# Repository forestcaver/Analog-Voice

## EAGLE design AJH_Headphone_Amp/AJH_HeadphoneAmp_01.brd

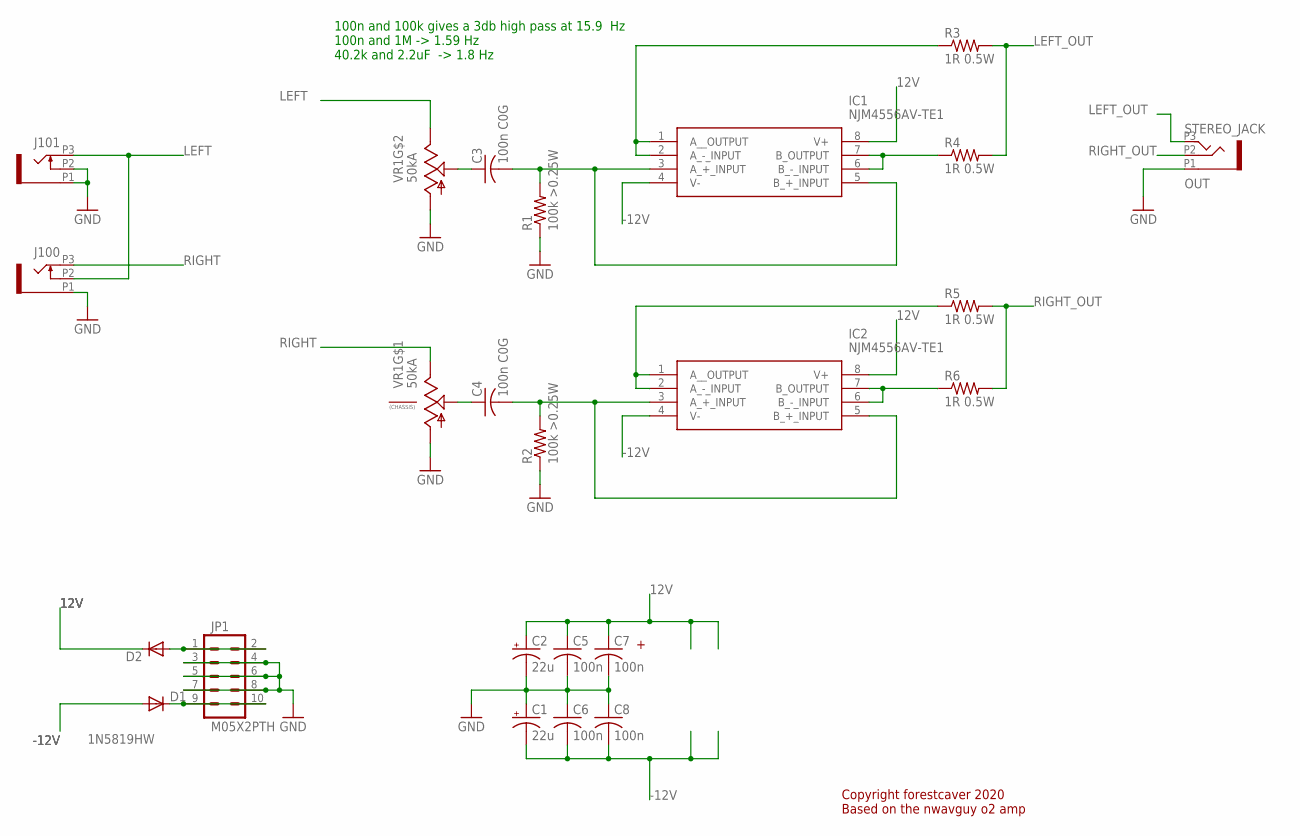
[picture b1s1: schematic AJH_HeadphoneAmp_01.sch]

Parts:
C1, C2: 22u; PANASONIC_B
C3, C4: 100n C0G; C1206
C5, C6, C7, C8: 100n; C0603
D1, D2: 1N5819HW; SOD123
IC1, IC2: NJM4556AV-TE1; SOP65P640X145-8N
J100, J101: PJ301_THONKICONN6; WQP_PJ_301M6
JP1: M05X2PTH; AVR_ICSP
OUT: STEREO_JACK; WQP_PJ_301M8
R1, R2: 100k >0.25W; R1206
R3, R4, R5, R6: 1R 0.5W; R1206
VR1: 50kA; DUAL_9MM_SNAP-IN_POT

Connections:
12V: C2.+, C5.1, C7.1, D2.C, IC1.8 (V+), IC2.8 (V+)
-12V: C1.-, C6.2, C8.2, D1.A, IC1.4 (V-), IC2.4 (V-)
GND: C1.+, C2.-, C5.2, C6.1, C7.2, C8.1, J100.P1 (1), J101.P1 (1), J101.P2 (2), JP1.3, JP1.4, JP1.5, JP1.6, JP1.7, JP1.8, OUT.P1 (1), R1.1, R2.1, VR1.1 (A), VR1.1B (A)
LEFT: J100.P2 (2), J101.P3 (3), VR1.3B (E)
LEFT_OUT: OUT.P3 (3), R3.2, R4.2
unnamed: C4.1, VR1.2 (S)
unnamed: C3.1, VR1.2B (S)
unnamed: C4.2, IC2.3 (A_+_INPUT), IC2.5 (B_+_INPUT), R2.2
unnamed: C3.2, IC1.3 (A_+_INPUT), IC1.5 (B_+_INPUT), R1.2
unnamed: IC1.6 (B_-_INPUT), IC1.7 (B_OUTPUT), R4.1
unnamed: D2.A, JP1.1, JP1.2
unnamed: IC2.1 (A__OUTPUT), IC2.2 (A_-_INPUT), R5.1
unnamed: IC2.6 (B_-_INPUT), IC2.7 (B_OUTPUT), R6.1
unnamed: IC1.1 (A__OUTPUT), IC1.2 (A_-_INPUT), R3.1
unnamed: D1.C, JP1.9, JP1.10
RIGHT: J100.P3 (3), VR1.3 (E)
RIGHT_OUT: OUT.P2 (2), R5.2, R6.2

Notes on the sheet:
100n and 100k gives a 3db high pass at 15.9 Hz 100n and 1M -> 1.59 Hz 40.2k and 2.2uF -> 1.8 Hz
Copyright forestcaver 2020 Based on the nwavguy o2 amp

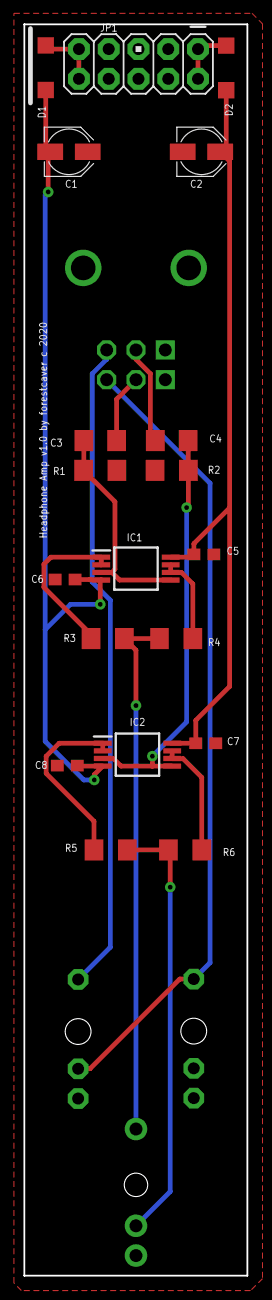
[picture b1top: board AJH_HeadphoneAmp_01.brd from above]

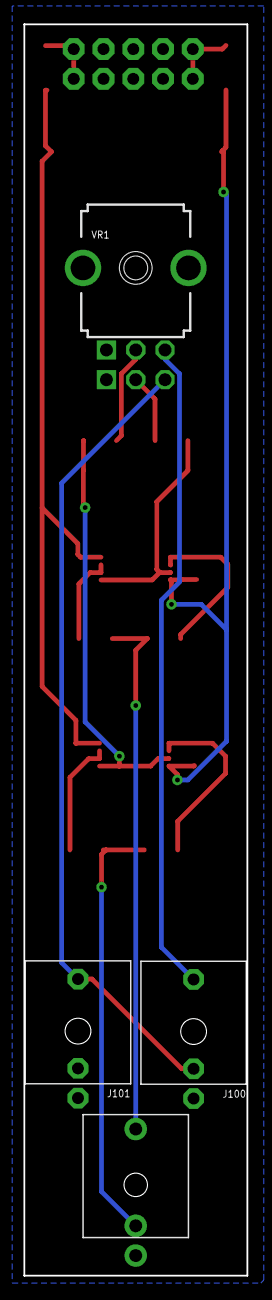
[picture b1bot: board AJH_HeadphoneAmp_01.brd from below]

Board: 2 copper layers, 19.0 x 106.8 mm, 23 parts (4 on the bottom side), 17 nets.

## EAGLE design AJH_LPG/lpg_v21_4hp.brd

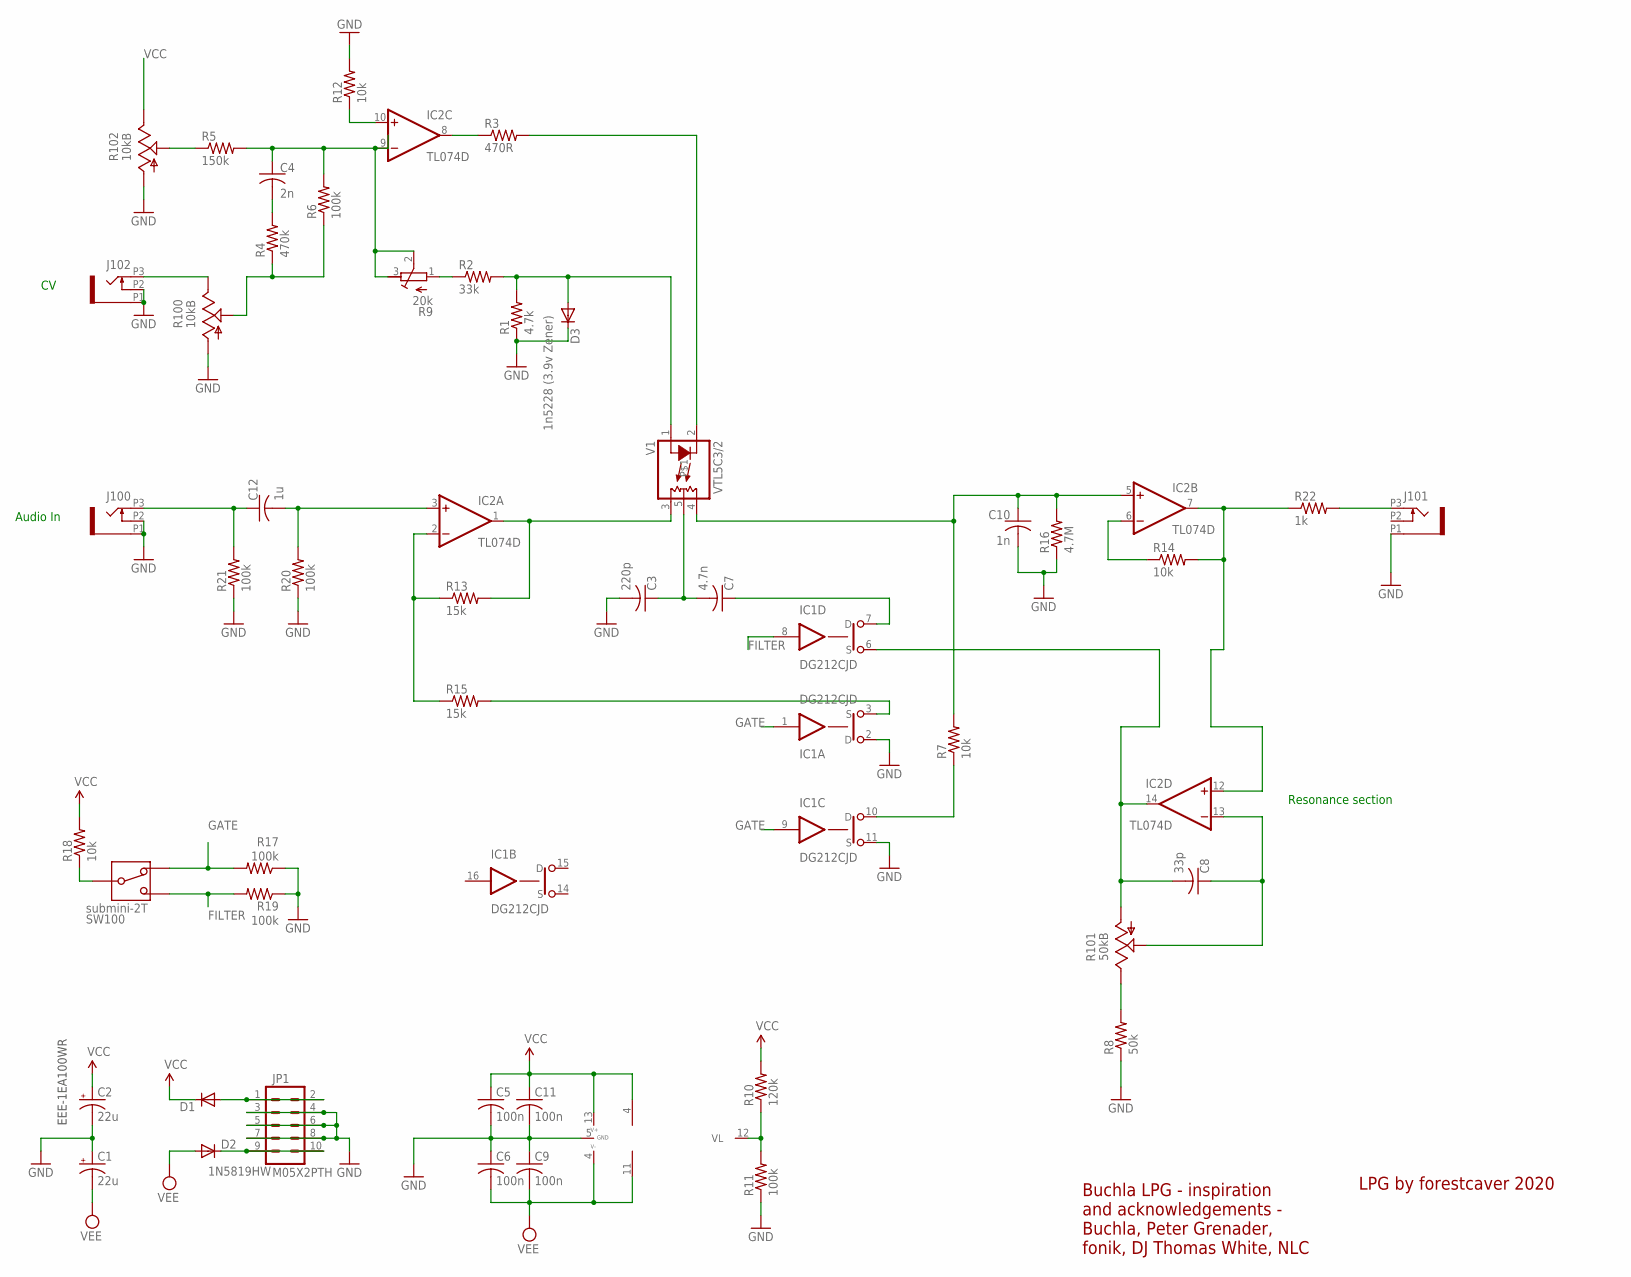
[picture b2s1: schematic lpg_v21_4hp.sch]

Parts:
C1, C2: 22u; PANASONIC_B; MPN EEE-FT1V220AR; MOUSER 667-EEE-FT1V220AR
C3: 220p; C0603
C4: 2n; C0603
C5, C6, C9, C11: 100n; C0603
C7: 4.7n; C0603
C8: 33p; C0603
C10: 1n; C0603
C12: 1u; C0603
D1, D2: 1N5819HW; SOD123
D3: 1n5228 (3.9v Zener); SOD123; MPN MMSZ5228BT1G; MOUSER 863-MMSZ5228BT1G
IC1: DG212CJD; SO16; MPN ADG212AKRZ-REEL; MOUSER 584-ADG212AKRZ-R
IC2: TL074D; SO14; MPN TL074CDR; MOUSER 595-TL074CDR
J100, J101, J102: PJ301_THONKICONN6; WQP_PJ_301M6
JP1: M05X2PTH; AVR_ICSP
R1: 4.7k; R0603
R2: 33k; R0603
R3: 470R; R0603
R4: 470k; R0603
R5: 150k; R0603
R6, R11, R17, R19, R20, R21: 100k; R0603
R7, R12, R14, R18: 10k; R0603
R8: 50k; R0603
R9: 20k; RTRIM3296X
R10: 120k; R0603
R13, R15: 15k; R0603
R16: 4.7M; R0603
R22: 1k; R0603
R100, R102: 10kB; ALPS_POT_VERTICAL_PS
R101: 50kB; ALPS_POT_VERTICAL_PS
SW100: submini-2T; SPDT-SUB
V1: VTL5C3/2; VACTROL_5PIN_VTL5C-2

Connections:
FILTER: IC1.8 (IN), R19.2, SW100.P$1
GATE: IC1.1 (IN), IC1.9 (IN), R17.2, SW100.P$3
GND: C1.+, C2.-, C3.2, C5.2, C6.1, C9.1, C10.2, C11.2, D3.C, IC1.2 (D), IC1.5 (GND), IC1.11 (S), J100.P1 (1), J100.P2 (2), J101.P1 (1), J102.P1 (1), J102.P2 (2), JP1.3, JP1.4, JP1.5, JP1.6, JP1.7, JP1.8, R1.1, R8.1, R11.1, R12.2, R16.1, R17.1, R19.1, R20.1, R21.1, R100.P$3 (A), R102.P$3 (A)
unnamed: IC1.3 (S), R15.2
unnamed: C8.2, IC1.6 (S), IC2.14 (OUT), R101.P$3 (A)
unnamed: IC1.10 (D), R7.1
unnamed: IC1.12 (VL), R10.1, R11.2
unnamed: J102.P3 (3), R100.P$1 (E)
unnamed: D1.A, JP1.1, JP1.2
unnamed: R18.1, SW100.P$2
unnamed: R5.1, R102.P$2 (S)
unnamed: C7.1, IC1.7 (D)
unnamed: C12.2, IC2.3 (+IN), R20.2
unnamed: R8.2, R101.P$1 (E)
unnamed: D2.C, JP1.9, JP1.10
unnamed: C4.2, R4.2
unnamed: R2.1, R9.1 (E)
unnamed: R4.1, R6.1, R100.P$2 (S)
unnamed: IC2.8 (OUT), R3.1
unnamed: IC2.10 (+IN), R12.1
unnamed: C4.1, IC2.9 (-IN), R5.2, R6.2, R9.2 (S), R9.3 (A)
unnamed: D3.A, R1.2, R2.2, V1.1 (A)
unnamed: R3.2, V1.2 (C)
unnamed: C12.1, J100.P3 (3), R21.2
unnamed: IC2.2 (-IN), R13.1, R15.1
unnamed: IC2.1 (OUT), R13.2, V1.3 (L1)
unnamed: C3.1, C7.2, V1.5
unnamed: J101.P3 (3), R22.2
unnamed: IC2.6 (-IN), R14.1
unnamed: IC2.7 (OUT), IC2.12 (+IN), R14.2, R22.1
unnamed: C10.1, IC2.5 (+IN), R7.2, R16.2, V1.4 (L2)
unnamed: C8.1, IC2.13 (-IN), R101.P$2 (S)
VCC: C2.+, C5.1, C11.1, D1.C, IC1.13 (V+), IC2.4 (V+), R10.2, R18.2, R102.P$1 (E)
VEE: C1.-, C6.2, C9.2, D2.A, IC1.4 (V-), IC2.11 (V-)

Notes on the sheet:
EEE-1EA100WR
Audio In
Resonance section
LPG by forestcaver 2020
Buchla LPG - inspiration and acknowledgements - Buchla, Peter Grenader, fonik, DJ Thomas White, NLC

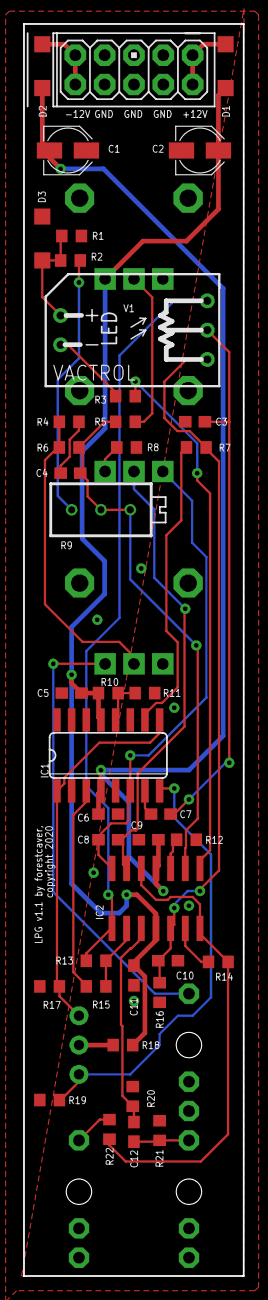
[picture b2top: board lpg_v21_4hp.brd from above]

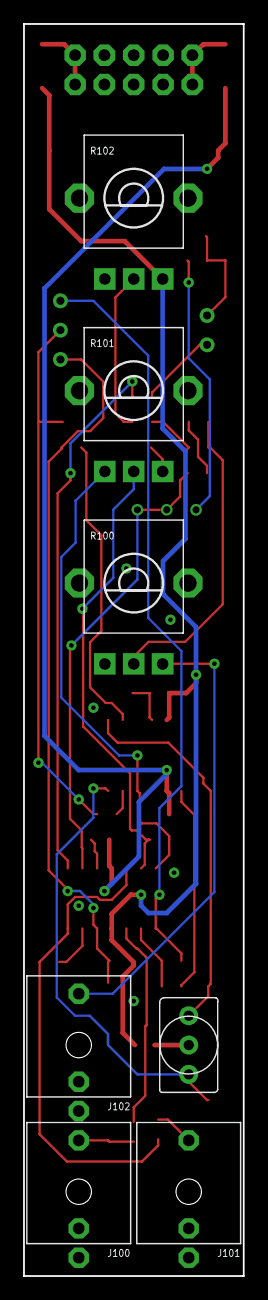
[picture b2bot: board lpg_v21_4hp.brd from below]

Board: 2 copper layers, 19.0 x 108.4 mm, 48 parts (7 on the bottom side), 34 nets.

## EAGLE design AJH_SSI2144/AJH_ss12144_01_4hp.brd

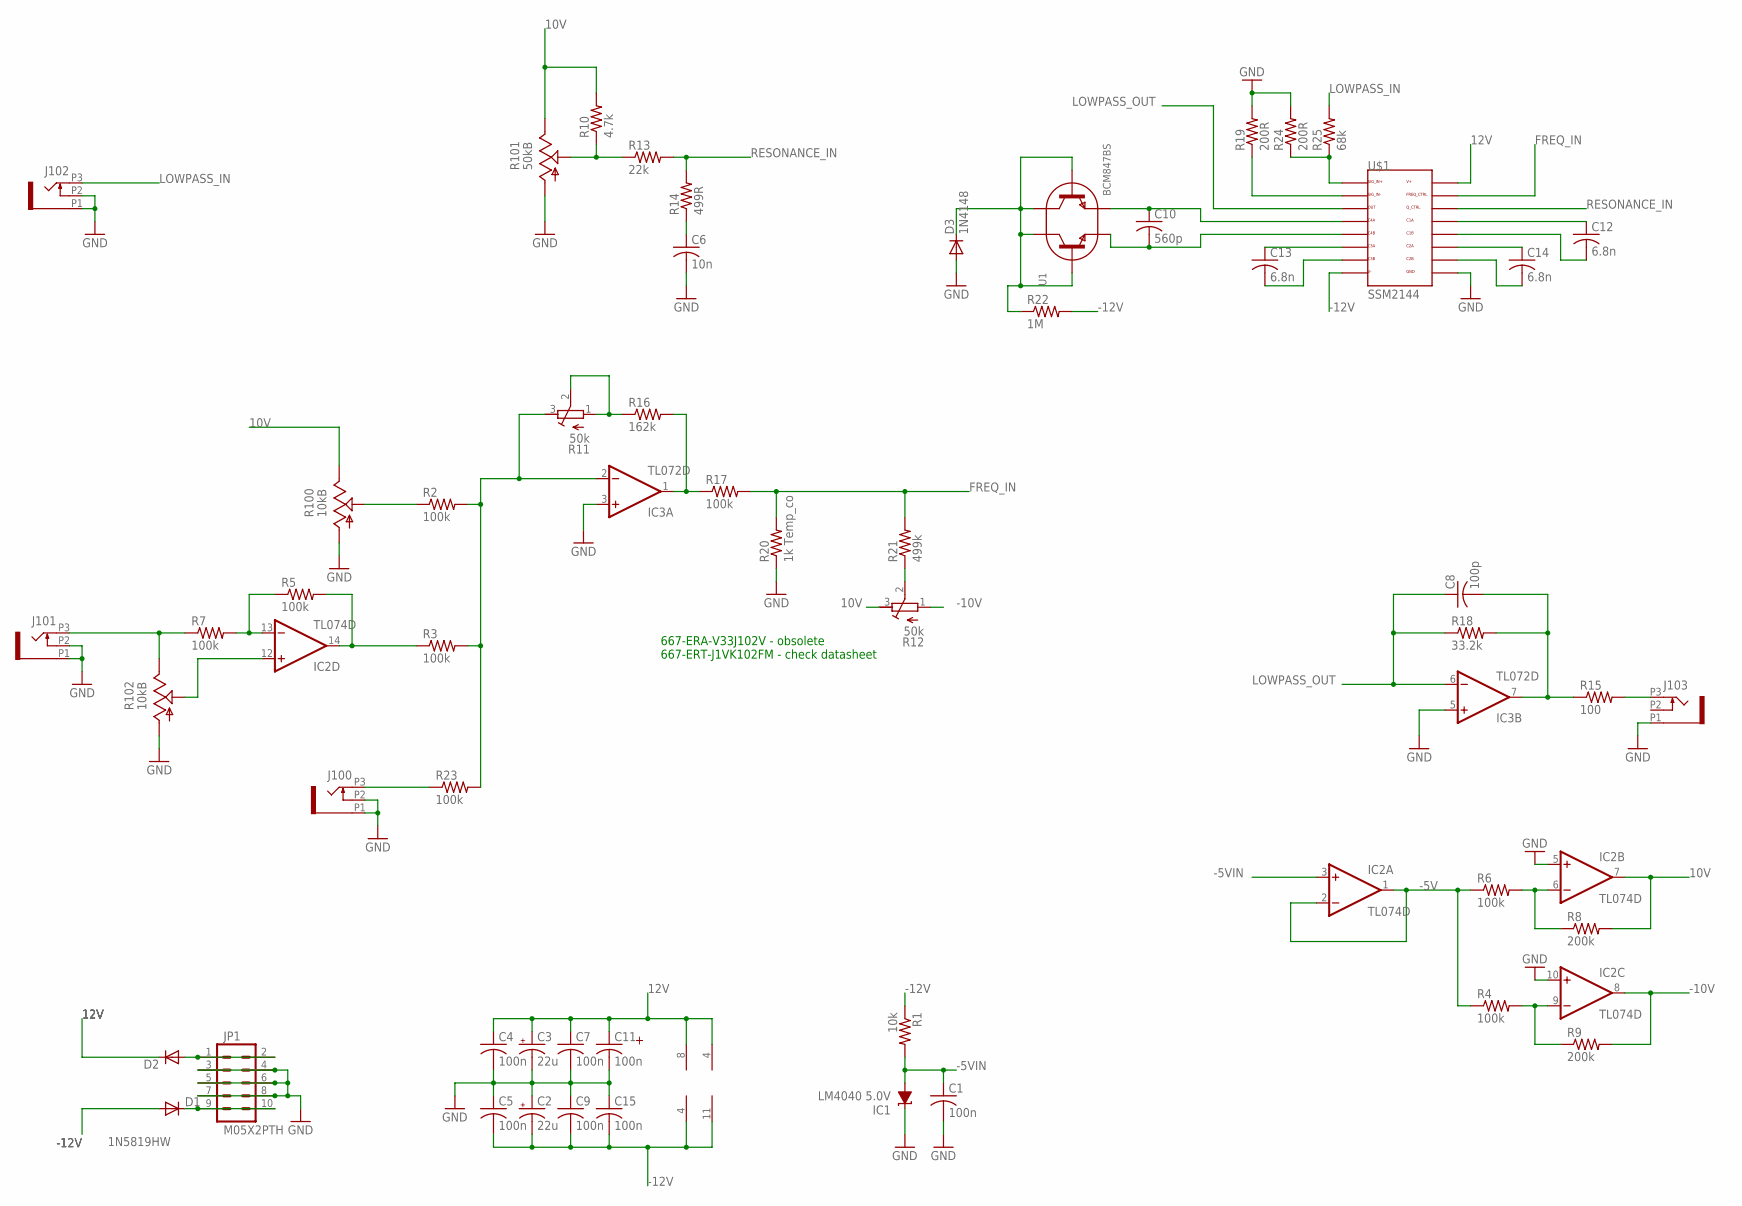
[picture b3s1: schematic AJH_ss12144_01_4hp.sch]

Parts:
C1, C4, C5, C7, C9, C11, C15: 100n; C0603
C2, C3: 22u; PANASONIC_B
C6: 10n; C0603
C8: 100p; C0603
C10: 560p; C0603
C12, C13, C14: 6.8n; C0603
D1, D2: 1N5819HW; SOD123
D3: 1N4148; SOD523
IC1: LM4040 5.0V; DBZ_R-PDSO-G3
IC2: TL074D; SO14
IC3: TL072D; SO08
J100, J101, J102, J103: PJ301_THONKICONN6; WQP_PJ_301M6
JP1: M05X2PTH; AVR_ICSP
R1: 10k; R0603
R2, R3, R4, R5, R6, R7, R17, R23: 100k; R0603
R8, R9: 200k; R0603
R10: 4.7k; R0603
R11, R12: 50k; RTRIM3296X
R13: 22k; R0603
R14: 499R; R0603
R15: 100; R0603
R16: 162k; R0603
R18: 33.2k; R0603
R19, R24: 200R; R0603
R20: 1k Temp_co; R0603
R21: 499k; R0603
R22: 1M; R0603
R25: 68k; R0603
R100, R102: 10kB; ALPS_POT_VERTICAL
R101: 50kB; ALPS_POT_VERTICAL
U1: BCM847BS; SOT363
U$1: SSM2144; SSOP16

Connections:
10V: IC2.7 (OUT), R8.2, R10.2, R12.3 (A), R100.P$1 (E), R101.P$1 (E)
12V: C3.+, C4.1, C7.1, C11.1, D2.C, IC2.4 (V+), IC3.8 (V+), U$1.16 (V+)
-5V: IC2.1 (OUT), IC2.2 (-IN), R4.1, R6.1
-5VIN: C1.1, IC1.2 (A), IC2.3 (+IN), R1.2
-10V: IC2.8 (OUT), R9.2, R12.1 (E)
-12V: C2.-, C5.2, C9.2, C15.2, D1.A, IC2.11 (V-), IC3.4 (V-), R1.1, R22.2, U$1.8 (V-)
FREQ_IN: R17.2, R20.2, R21.2, U$1.15 (FREQ_CTRL)
GND: C1.2, C2.+, C3.-, C4.2, C5.1, C6.2, C7.2, C9.1, C11.2, C15.1, D3.A, IC1.1 (C), IC2.5 (+IN), IC2.10 (+IN), IC3.3 (+IN), IC3.5 (+IN), J100.P1 (1), J100.P2 (2), J101.P1 (1), J101.P2 (2), J102.P1 (1), J102.P2 (2), J103.P1 (1), JP1.3, JP1.4, JP1.5, JP1.6, JP1.7, JP1.8, R19.2, R20.1, R24.2, R100.P$3 (A), R101.P$3 (A), R102.P$3 (A), U$1.9 (GND)
LOWPASS_IN: J102.P3 (3), R25.2
LOWPASS_OUT: C8.1, IC3.6 (-IN), R18.1, U$1.3 (OUT)
unnamed: C8.2, IC3.7 (OUT), R15.1, R18.2
unnamed: C13.1, U$1.6 (C3A)
unnamed: IC2.12 (+IN), R102.P$2 (S)
unnamed: R2.1, R100.P$2 (S)
unnamed: IC2.13 (-IN), R5.1, R7.2
unnamed: D2.A, JP1.1, JP1.2
unnamed: IC3.2 (-IN), R2.2, R3.2, R11.3 (A), R23.2
unnamed: IC3.1 (OUT), R16.2, R17.1
unnamed: C10.1, U1.4 (E2), U$1.4 (C4A)
unnamed: J100.P3 (3), R23.1
unnamed: J103.P3 (3), R15.2
unnamed: IC2.14 (OUT), R3.1, R5.2
unnamed: IC2.9 (-IN), R4.2, R9.1
unnamed: D3.C, R22.1, U1.2 (B1), U1.3 (C2), U1.5 (B2), U1.6 (C1)
unnamed: IC2.6 (-IN), R6.2, R8.1
unnamed: C10.2, U1.1 (E1), U$1.5 (C4B)
unnamed: C13.2, U$1.7 (C3B)
unnamed: C14.2, U$1.10 (C2B)
unnamed: C14.1, U$1.11 (C2A)
unnamed: D1.C, JP1.9, JP1.10
unnamed: C12.1, U$1.13 (C1A)
unnamed: C12.2, U$1.12 (C1B)
unnamed: R19.1, U$1.2 (SIG_IN-)
unnamed: R10.1, R13.1, R101.P$2 (S)
unnamed: C6.1, R14.1
unnamed: R12.2 (S), R21.1
unnamed: R24.1, R25.1, U$1.1 (SIG_IN+)
unnamed: R11.1 (E), R11.2 (S), R16.1
unnamed: J101.P3 (3), R7.1, R102.P$1 (E)
RESONANCE_IN: R13.2, R14.2, U$1.14 (Q_CTRL)

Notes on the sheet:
667-ERA-V33J102V - obsolete 667-ERT-J1VK102FM - check datasheet

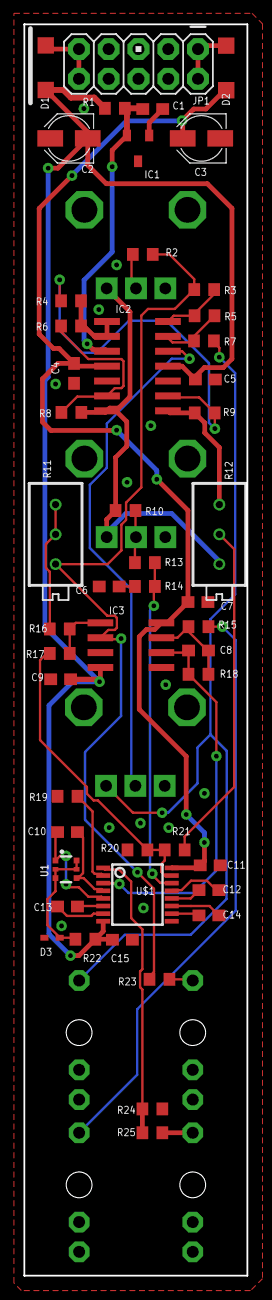
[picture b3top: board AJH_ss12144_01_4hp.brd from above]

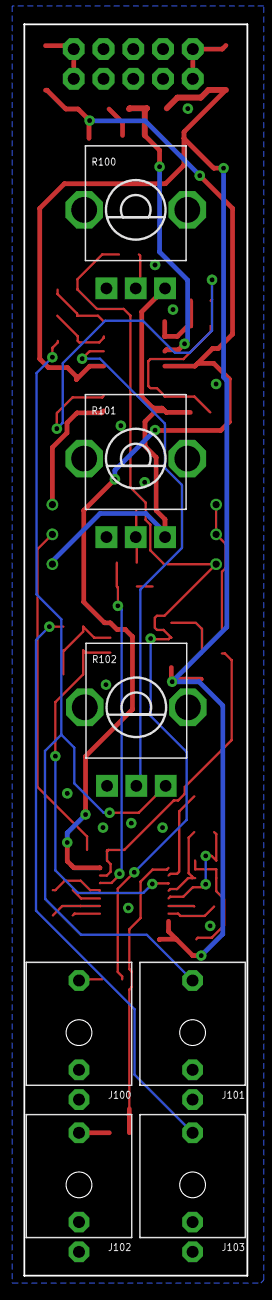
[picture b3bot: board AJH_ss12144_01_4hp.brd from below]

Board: 2 copper layers, 19.0 x 106.8 mm, 56 parts (7 on the bottom side), 40 nets.

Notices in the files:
AJH_LPG/lpg_v21_4hp.brd:
LPG v1.1 by forestcaver,
copyright 2020
